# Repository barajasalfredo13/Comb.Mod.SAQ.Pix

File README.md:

# Comb.Mod.SAQ.Pix

✨::: Updates :::✨  

This is a demo photo of the current system design.    
  
## Table of Contents  
- [Current Assets]
  - 🟢[Pixel Combs]   
  - 🟡[Readout Feedthrough]    
  - 🟠[Steel Vessel]  
- [Planned Development]  
  - 📝[19 Channel SAQ Board] or [2-Three Channel, 2-Four Channel, 1-Five Channel]  
  - 📝[Source Holder] 
- [Research and Development Tools]
  - 🟢[Pixel Shadow Masks] 
- [Optional Testing Equipment]
  - 🟢[Channel Tester] 
- [Icon Legend]

## Current Assets   
### 🟢 - **[Pixel Combs](/Modular.Pixel.Combs/):** ./Modular.Pixel.Combs/  

:: Base Geometry and Dimensions ::  
PCB.Dimensions : 78 x 78 mm  
PCB.Thickness : 1.6 mm  
(Outer Radius) : 39 mm  
(Inner Radius) : 30 mm  
Pixel Pitch : 10 mm  

Pixel Description :::  
A- Solid Single Conductive Plane Hexagon  
B- Solid Single Conductive Plane Hexagon with Single Biased Hexagon Ring  
C- Solid Single Circular Plane with Single Biased Hexagon Ring  
  
::: Intended Use :::  
Pixel Comb planes were designed to be used as experimental collection planes for specific interactions. With use of shadow masks, we can deposite materials to experimentally test. measure and characterize novel materials.  

--------------  
### ✨ 🟡 - **[Readout Feedthrough](/Readout.Feed.Through.Adapter/):** ./Readout.Feed.Through.Adapter/  

✨ **Description of the PCB Component**  
  
:: Base Geometry and Dimensions ::  
PCB.Dimensions : [A] 80 x 80 mm ::: [B] 68 x 68 mm  
PCB.Thickness : [A] 1.6 mm  ::: [B] 1.6 mm  

<a href="https://www.digikey.com/en/products/detail/mill-max-manufacturing-corp/0906-1-15-20-75-14-11-0/1147049">Pogo Pins used for design [Digi-Key]</a>  
  
#### ::: Assembly Instructions :::  [Pictures and Diagrams Coming soon]  
Note: Each PCB should have text on which side faces the metal, additionally they are keyed.  
1- Solder (Avoid Zinc Based Solders) Pogo Pins and a necessary amount of wire so that you have enough cable to go through the metallic component.  
2- Clean all components in an ethanol bath and store in a clean area.  
3- Prepare enough epoxy to fill the holes in the metal part of the readout adapter.  
4- Align the PCB with the wires and secure firmly to the metal adapter.  
5- Flip the device over and pour epoxy to the top.  
6- While epoxy is still wet, align the wires and place the second PCB.  
7- Secure tightly and allow to dry for the recommended time.   

--------------  
### 🟠 - **[Steel Vessel](/Vessel.Full/Fusion360/):** ./2.Fusion360/Vessel/Smooth.SAQ.Pix.Vessel.5.15.2023     
   
img updated: 5/15/2023  
  
Vessel will be modified so that Standardized Feedthroughs can be used.   
  
--------------- 
## Planned Development
📝 - [19 Channel SAQ Board] or [2-Three Channel, 2-Four Channel, 1-Five Channel]  
📝 - Source Holder   

---------------  
## Research and Development Tools  
### 🟢- **[Pixel Shadow Masks](/Shadow.Mask.Kit/Fusion360/)** ./Shadow.Mask.Kit/Fusion360/  
    
  Material ::: 316L Stainless Steel   
  Shadow Mask Thickness ::: [ 0.015 in // 0.381 mm ]  

316L Stainless Steel was chosen due to its low outgassing and resistiveness to corrosion  
  
:: [Drawings](/Shadow.Mask.Kit/Drawings/) ::  
Demo of Shadow Mask Designs  

Shadow Mask Holder Drawing    

⚠️ Ground Stencil is not Made ⚠️  
A shadow mask for the ground section of these boards cannot be made due to the geometry.  
  
----------------  
## Optional Testing Equipment  
  
### 🟢- **[Channel Tester](/Channel.Tester/KiCAD/):** ./Channel.Tester/KiCAD  
   
:: Base Geometry and Dimensions ::  
PCB.Dimensions : 78 x 78 mm  

#### How to Use
Note: The Channel Tester has the same dimensions of a pixel board  
1- Insert the Channel Tester board and secure it like a pixel board.  
2- Send test signals in a labeled slot, record the channel triggered  
  ex: Slot A receives input, channel 7 is triggered. -> A7  
3- When each letter has a number assigned, you can begin tests.  

---------------  
## Icon Legend  
|   Legend       |  Meaning                      |
|----------------|-------------------------------|
|✨| Recently Updated / New Items            |
|📝| This component is in the design and illustration phase            |
|🟠| This component is under development            |
|⚠️| This component requires feedback before further development |
|🟡| This component files are under final review |
|🟢| This component's design is final |

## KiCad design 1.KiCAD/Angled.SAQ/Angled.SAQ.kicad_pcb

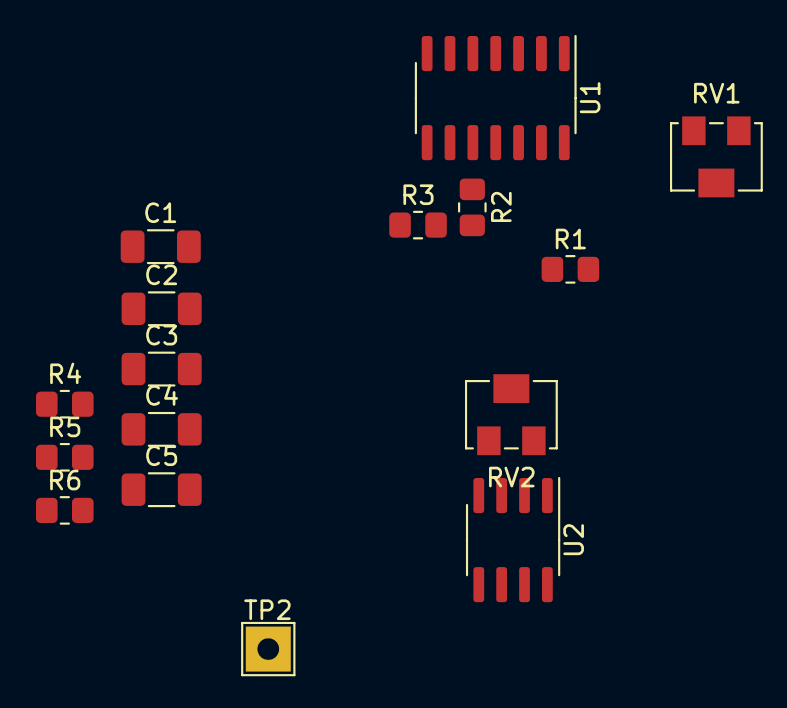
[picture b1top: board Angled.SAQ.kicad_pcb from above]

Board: 2 copper layers, 16 parts (0 on the bottom side), 12 nets, no tracks yet.

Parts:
C1: 10n; C_1206_3216Metric_Pad1.33x1.80mm_HandSolder
C2, C3, C4, C5: 0.1u; C_1206_3216Metric_Pad1.33x1.80mm_HandSolder
R1, R5: 50; R_0805_2012Metric_Pad1.20x1.40mm_HandSolder
R2: 3k; R_0805_2012Metric_Pad1.20x1.40mm_HandSolder
R3, R6: 1k; R_0805_2012Metric_Pad1.20x1.40mm_HandSolder
R4: 2.2k; R_0805_2012Metric_Pad1.20x1.40mm_HandSolder
RV1, RV2: 0->10k; Potentiometer_Bourns_3214W_Vertical
TP2: TestPoint_Alt; TestPoint_THTPad_2.5x2.5mm_Drill1.2mm
U1: IVC102; SOIC-14_3.9x8.7mm_P1.27mm
U2: AD8561; SOIC-8_3.9x4.9mm_P1.27mm

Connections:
+9V: C4.1, R6.2, U2.1 (V+)
+15V: C2.1, U1.14 (+V)
-15V: C3.1, U1.9 (-V)
GND: C2.2, C3.2, C4.2, C5.2, R3.1, RV2.1, RV2.2, U1.1 (int_p), U1.2 (int_n'), U1.7 (nc), U1.8 (GNDA), U2.4 (V-)
GNDD: R4.2, RV1.1, RV1.2, U1.13 (GNDD), U2.6 (GND)
unnamed: R2.1, U1.10 (OUT)
unnamed: R1.1, U1.12 (S2)
unnamed: R2.2, R3.2, U2.2 (+)
unnamed: C1.1, R4.1, RV1.3, U2.5 (LATCH)
unnamed: C1.2, R5.1, U2.7 (Q)
unnamed: R1.2, U2.8 (~Q)
VDD: C5.1, R6.1, RV2.3, TP2.1, U2.3 (-)

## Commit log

2023-04-25 Added Base files for Comb Mod
2023-04-26 Refilled Copper Zones
2023-04-26 Minor Changes
2023-04-27 Updated Combs
2023-04-27 Removed 1 file
2023-04-27 added timelines
2023-04-27 Added README images
2023-04-27 Spaced collection board traces
2023-04-28 Thickened ground traces and updated channel wires
2023-04-30 Started Designing Vessel. Minor Updates
2023-05-01 Started and Finished Base Enclosure
2023-05-04 Updated Status
2023-05-09 Added a second design of the Steel Vessel
2023-05-09 Updated ReadME Image
2023-05-09 Updated Fusion360 Files. Added Gasket support for vessel 2
2023-05-10 Added STL files for 3D view of current SAQ-Vessel
2023-05-10 fixed READme errors
2023-05-10 Cleaned Some Files
2023-05-10 Updated to Newer Model, Deleted Old Model
2023-05-10 Added new model, Cleaned drawings
2023-05-10 Updated 3D render model, Updated Feedthrough Image
2023-05-10 Fixed Render Error for 3D Viewer
2023-05-11 Added collection Feedthrough Adapter
2023-05-11 Updated Readout Adapter for better Vaccum hold
2023-05-11 Removed unused and outdated assets
2023-05-11 added pogo pin digikey link
2023-05-12 Created Pixel Holder in new Fusion360 file
2023-05-12 Major changes to readout design
2023-05-15 Cleaned old files and updated ReadME to current model
2023-05-15 Added Channel Tester
2023-05-15 Updated texts on files
2023-05-15 Updated Fusion360 File /// Cleaned some Other Files
2023-05-19 Uploaded a Simplified Model
2023-05-21 Major Update for Files
2023-05-21 Added Drawings Demo
2023-05-21 Smoothed out Hexagon Pixels so that it Better Fits the Stencils
2023-05-22 Finalized Pixel Plane Design
2023-05-23 Updated Readout adapter info
2023-05-23 Fixed Readme
2023-05-23 Minor Fixes
2023-06-01 Updated Stenecil Holder Drawings
2023-06-01 Improved Readability
2023-06-09 Updated ReadoutPCBs to allow smoother gasflow
